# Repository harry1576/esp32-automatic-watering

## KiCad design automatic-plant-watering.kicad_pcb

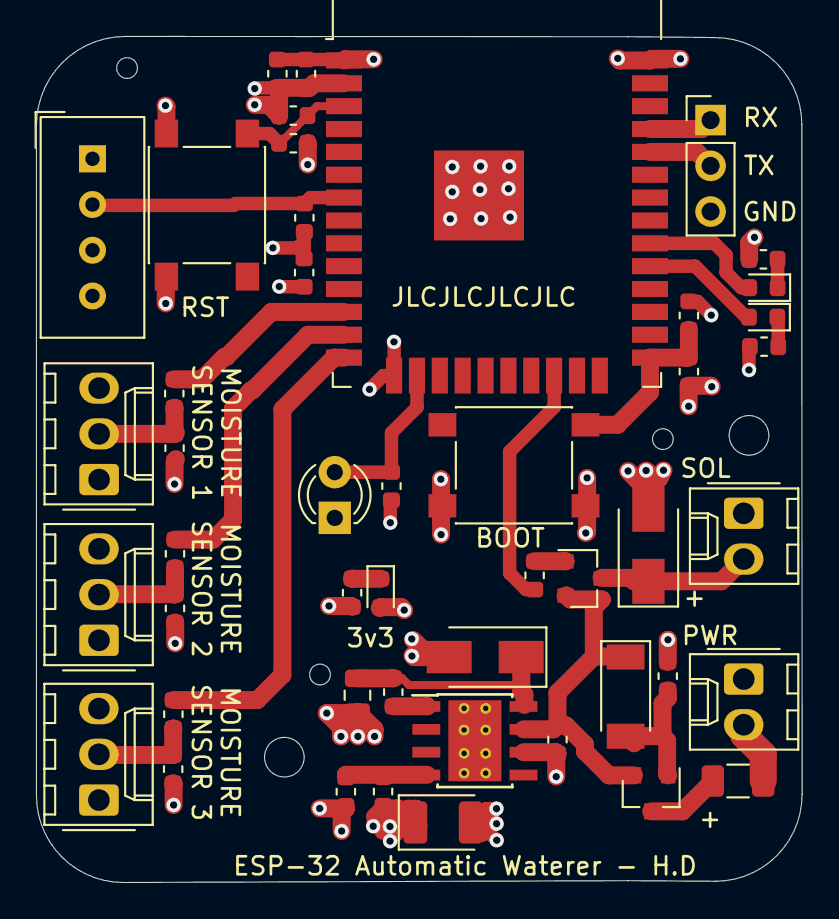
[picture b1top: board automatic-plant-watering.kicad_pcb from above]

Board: 4 copper layers, 42.5 x 47.0 mm, 49 parts (0 on the bottom side), 29 nets.

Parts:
C1, C3, C7, C20: 10u; C_0603_1608Metric
C2, C5, C8, C9, C10: 100n; C_0603_1608Metric
C4: 10n; C_0603_1608Metric
C6: 100u; CP_EIA-3528-21_Kemet-B
D1, D2, D6: RED; LED_0603_1608Metric
D3: D_Zener; D_SOD-128
D4: B340; D_SMA
D5: D_Small; D_SMA
F1: 3A; Fuse_1206_3216Metric
H1: TR; MountingHole_2.2mm_M2_DIN965
H4: BL; MountingHole_2.2mm_M2_DIN965
J1, J3: Power; Molex_KK-254_AE-6410-02A_1x02_P2.54mm_Vertical
J2: PROG; PinHeader_1x03_P2.54mm_Vertical
J4, J8, J9: INPUT; Molex_KK-254_AE-6410-03A_1x03_P2.54mm_Vertical
L1: L_Small; L_0805_2012Metric
Q1, Q2: AO3401A; SOT-23
Q3: TEPT4400; LED_D3.0mm_Clear
R1, R2, R3, R4, R9, R10, R12, R14, R15: 10k; R_0603_1608Metric
R5, R6, R7: 220; R_0603_1608Metric
R11: 3.9k; R_0603_1608Metric
R13: 5.6k; R_0603_1608Metric
SW1, SW2: SW_Push; SW_Push_1P1T_NO_6x6mm_H9.5mm
U1: ESP32-WROOM-32D; ESP32-WROOM-32
U2: TPS5430DDA; TI_SO-PowerPAD-8_ThermalVias
U4: DHT11; Aosong_DHT11_5.5x12.0_P2.54mm

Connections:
12V_IN: C3.1, D3.1, Q1.2, Q2.2, U2.7
+3V3: C1.1, C2.1, C5.1, C6.1, D6.2, J4.1, J8.1, J9.1, L1.2, Q3.1, R1.1, R3.1, R9.1, R12.1, U1.2, U4.1
DRIVER: R4.2, U1.22
GND: C1.2, C2.2, C3.2, C5.2, C6.2, C7.2, C8.2, C9.2, C10.2, C20.2, D4.2, D5.2, J1.1, J2.3, J3.1, J4.3, J8.3, J9.3, R2.2, R5.1, R6.1, R7.1, R11.2, R13.2, SW1.2, SW2.2, U1.1, U1.15, U1.38, U1.39, U2.6, U2.9, U4.4
GPIO0: C7.1, R3.2, SW2.1, U1.25
LIGHT_SENSOR: Q3.2, R11.1, U1.16
MOIST1: R15.1, U1.14
MOIST2: R14.1, U1.13
MOIST3: R10.1, U1.12
unnamed: C4.1, D4.1, L1.1, U2.8
unnamed: C4.2, U2.1
unnamed: C8.1, J4.2, R10.2
unnamed: C9.1, J8.2, R14.2
unnamed: C10.1, J9.2, R15.2
unnamed: D1.1, R6.2
unnamed: D1.2, U1.29
unnamed: D2.1, R7.2
unnamed: D2.2, U1.30
unnamed: D3.2, Q1.1, R2.1
unnamed: D5.1, J3.2, Q2.3
unnamed: D6.1, R5.2
unnamed: F1.1, Q1.3
unnamed: F1.2, J1.2
unnamed: Q2.1, R4.1
unnamed: R12.2, R13.1, U2.4
RESET: C20.1, R9.2, SW1.1, U1.3
RX_PROG: J2.1, U1.35
TEMP_HUMID_SEN: R1.2, U1.7, U4.2
TX_PROG: J2.2, U1.34

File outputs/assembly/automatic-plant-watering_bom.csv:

Comment,Designator,Footprint,LCSC
10u,"C1,C3,C7,C20",Capacitor_SMD:C_0603_1608Metric,C96446
10n,C4,Capacitor_SMD:C_0603_1608Metric,C57112
100n,"C2,C5,C8,C9,C10",Capacitor_SMD:C_0603_1608Metric,C30926
100u,C6,Capacitor_Tantalum_SMD:CP_EIA-3528-21_Kemet-B,C16133
RED,"D1,D2,D6",LED_SMD:LED_0603_1608Metric,C2286
D_Zener,D3,Diode_SMD:D_SOD-128,C253489
B340,D4,Diode_SMD:D_SMA,C64982
D_Small,D5,Diode_SMD:D_SMA,C64982
3A,F1,Fuse:Fuse_1206_3216Metric,C207036
TR,H1,MountingHole:MountingHole_2.2mm_M2_DIN965,
BL,H4,MountingHole:MountingHole_2.2mm_M2_DIN965,
Power,"J1,J3",Connector_Molex:Molex_KK-254_AE-6410-02A_1x02_P2.54mm_Vertical,
PROG,J2,Connector_PinHeader_2.54mm:PinHeader_1x03_P2.54mm_Vertical,
INPUT,"J4,J8,J9",Connector_Molex:Molex_KK-254_AE-6410-03A_1x03_P2.54mm_Vertical,
L_Small,L1,Inductor_SMD:L_0805_2012Metric,C32375
AO3401A,"Q1,Q2",Package_TO_SOT_SMD:SOT-23,C2997136
TEPT4400,Q3,LED_THT:LED_D3.0mm_Clear,
3.9k,R11,Resistor_SMD:R_0603_1608Metric,C23018
5.6k,R13,Resistor_SMD:R_0603_1608Metric,C23189
220,"R5,R6,R7",Resistor_SMD:R_0603_1608Metric,C4190
10k,"R1,R2,R3,R4,R9,R10,R12,R14,R15",Resistor_SMD:R_0603_1608Metric,C25197
SW_Push,"SW1,SW2",Button_Switch_SMD:SW_Push_1P1T_NO_6x6mm_H9.5mm,C843627
ESP32-WROOM-32D,U1,RF_Module:ESP32-WROOM-32,
TPS5430DDA,U2,Package_SO:TI_SO-PowerPAD-8_ThermalVias,C9864
DHT11,U4,Sensor:Aosong_DHT11_5.5x12.0_P2.54mm,

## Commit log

2022-07-17 removing USB to UART
2022-07-17 added 3d model
2022-07-19 fixed up some mistakes
